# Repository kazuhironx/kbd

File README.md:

# kbd

自作キーボード設計用のリポジトリです。

最初の対象は、Lily58 系より少しだけ記号に強い左右分割キーボードです。HHKB US 配列に慣れた Emacs 利用を前提に、column staggered の分割配列と、手持ちの SA Symbiosis / ortho 系キーキャップを活かす設計にします。

## 方針

- 左右分割、現行 Ergogen 案は片手 31 キー、合計 62 キー
- 有線 USB 接続
- 左右間接続は TRRS または JST を比較し、初期生成物は TRRS
- Keebio RP2040 Pro Micro 16MB を第一候補にした Pro Micro 互換フットプリント
- MX 5-pin direct solder
- plateless、1.6mm PCB、4mm spacer、1.6mm FR4 bottom plate
- LED、OLED、ロータリーエンコーダ、無線、電池は v1 では入れない
- `Space` は 2u キーキャップの優先候補
- `Ctrl` と `Enter` は 1u / 1.5u の差し替え候補として扱い、キーキャップ高さ確認後に確定する
- `[` と `]` は G/H の内側人差し指キーとして Base layer に置く
- 親指クラスタは片手 5 キーを残すが、常用は 3 キーまでに絞る
- 左親指 `Ctrl` と右親指 `Space` は 2u の対称配置にする
- `-` / `+` は T/Y の内側に置き、レイヤなしで押せる記号枠として扱う
- Ergogen の `ergogen/config.yaml` を物理配置とPCB外形の一次情報にする

## ディレクトリ

- `docs/`: レイアウト、キーキャップ、ピン割り当ての設計メモ
- `ergogen/`: 物理レイアウト、PCB外形、生成用設定
- `hardware/split60_ortho/`: KiCad プロジェクト
- `firmware/qmk/kazuhironx_split60_ortho/`: QMK キーボード定義の雛形

## Ergogen

```sh
npm install
npm run ergogen
```

確認用SVGは `docs/generated/` に、KiCadで開く生成PCBは `hardware/split60_ortho/generated/` に置きます。

## 次の作業

1. `docs/generated/split60-preview.svg` で親指クラスタと内側記号キーの位置を確認する。
2. KiCad 10.0.1 で `hardware/split60_ortho/generated/split60_left.kicad_pcb` を開き、外形、MX、ダイオード、MCU、TRRS位置を確認する。
3. Keebio RP2040 Pro Micro 16MB の実寸とUSB-C逃げに合わせてMCU位置を詰める。
4. 回路図、配線、DRC、Gerber出力へ進む。

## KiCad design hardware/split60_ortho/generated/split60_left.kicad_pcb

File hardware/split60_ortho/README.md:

# split60_ortho hardware

KiCad 用の作業ディレクトリです。

v1 の回路設計対象:

- 左右別基板
- Keebio RP2040 Pro Micro 16MB 第一候補の Pro Micro 互換フットプリント
- TRRS ジャック
- RESET スイッチ
- 片手31キー分の MX 5-pin direct solder
- 各キーのダイオード
- LED / OLED / encoder / wireless はなし

`generated/split60_left.kicad_pcb` は Ergogen から生成した初期PCBです。KiCad 10.0.1で開き、MCU位置、USB-C逃げ、ねじ穴、底板逃げを確認してから本配線へ進みます。

回路図作成後に ERC を実行し、QMK の matrix と一致していることを確認します。

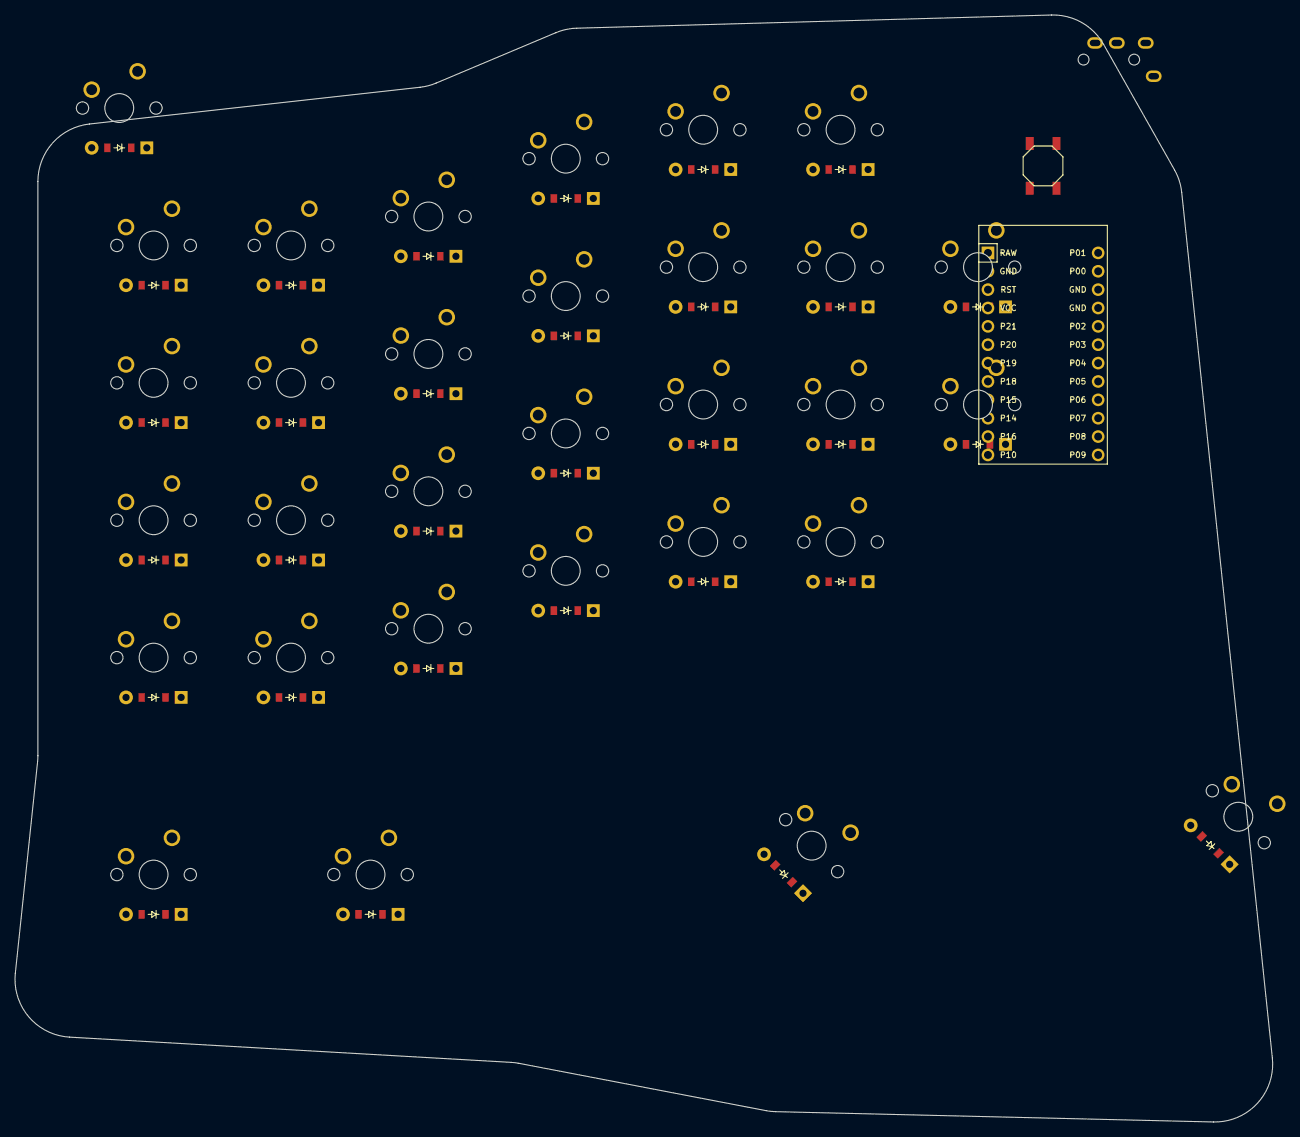
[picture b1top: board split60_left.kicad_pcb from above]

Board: 2 copper layers, 173.9 x 153.1 mm, 65 parts (0 on the bottom side), 46 nets, no tracks yet.

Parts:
B1: SW_TACT_ALPS_SKQGABE010
D1, D2, D3, D4, D5, D6, D7, D8, D9, D10, D11, D12, D13, D14, D15, D16, D17, D18, D19, D20, D21, D22, D23, D24, D25, D26, D27, D28, D29, D30, D31: ComboDiode
MCU1: ProMicro
S1, S2, S3, S4, S5, S6, S7, S8, S9, S10, S11, S12, S13, S14, S15, S16, S17, S18, S19, S20, S21, S22, S23, S24, S25, S26, S27, S28, S29, S30, S31: MX
TRRS1: TRRS-PJ-320A-dual

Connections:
C0: S1.1, S2.1, S3.1, S4.1, S5.1, S28.1
C1: S6.1, S7.1, S8.1, S9.1, S29.1
C2: S10.1, S11.1, S12.1, S13.1, S30.1
C3: S14.1, S15.1, S16.1, S17.1, S31.1
C4: S18.1, S19.1, S20.1, S21.1, S26.1, S27.1
C5: S22.1, S23.1, S24.1, S25.1
GND: B1.2, MCU1.2, MCU1.15, MCU1.16, TRRS1.2, TRRS1.4
P2: MCU1.17, TRRS1.3
R0: D4.1, D9.1, D13.1, D17.1, D21.1, D25.1
R1: D3.1, D8.1, D12.1, D16.1, D20.1, D24.1, D27.1
R2: D2.1, D7.1, D11.1, D15.1, D19.1, D23.1, D26.1
R3: D1.1, D6.1, D10.1, D14.1, D18.1, D22.1
R4: D28.1, D29.1, D30.1, D31.1
RST: B1.1, MCU1.3
VCC: MCU1.4, TRRS1.1
matrix_index_bottom: D18.2, S18.2
matrix_index_home: D19.2, S19.2
matrix_index_number: D21.2, S21.2
matrix_index_top: D20.2, S20.2
matrix_inner_bottom: D22.2, S22.2
matrix_inner_home: D23.2, S23.2
matrix_inner_number: D25.2, S25.2
matrix_inner_top: D24.2, S24.2
matrix_middle_bottom: D14.2, S14.2
matrix_middle_home: D15.2, S15.2
matrix_middle_number: D17.2, S17.2
matrix_middle_top: D16.2, S16.2
matrix_outer_bottom: D1.2, S1.2
matrix_outer_home: D2.2, S2.2
matrix_outer_mod: D5.2, S5.2
matrix_outer_number: D4.2, S4.2
matrix_outer_top: D3.2, S3.2
matrix_pinky_bottom: D6.2, S6.2
matrix_pinky_home: D7.2, S7.2
matrix_pinky_number: D9.2, S9.2
matrix_pinky_top: D8.2, S8.2
matrix_ring_bottom: D10.2, S10.2
matrix_ring_home: D11.2, S11.2
matrix_ring_number: D13.2, S13.2
matrix_ring_top: D12.2, S12.2
matrix_symbol_home: D26.2, S26.2
matrix_symbol_top: D27.2, S27.2
thumb_alt: D28.2, S28.2
thumb_ctrl: D30.2, S30.2
thumb_fn: D31.2, S31.2
thumb_lower: D29.2, S29.2

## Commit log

2026-05-08 Initial keyboard project scaffold
2026-05-08 Add layout draft drawing
2026-05-08 Revise layout to split 60
2026-05-08 Refine mirrored thumb cluster
2026-05-08 Move minus plus to inner index keys
2026-05-08 Update QMK scaffold for current keyboard json
2026-05-09 Add Ergogen split keyboard layout
2026-05-09 Lower inner index columns
2026-05-09 Refine column stagger and thumb outline
2026-05-10 Rework QWERT stagger and thumb cluster
2026-05-11 Increase Ergogen mirror preview gap
2026-05-11 Adjust thumb cluster preview layout
